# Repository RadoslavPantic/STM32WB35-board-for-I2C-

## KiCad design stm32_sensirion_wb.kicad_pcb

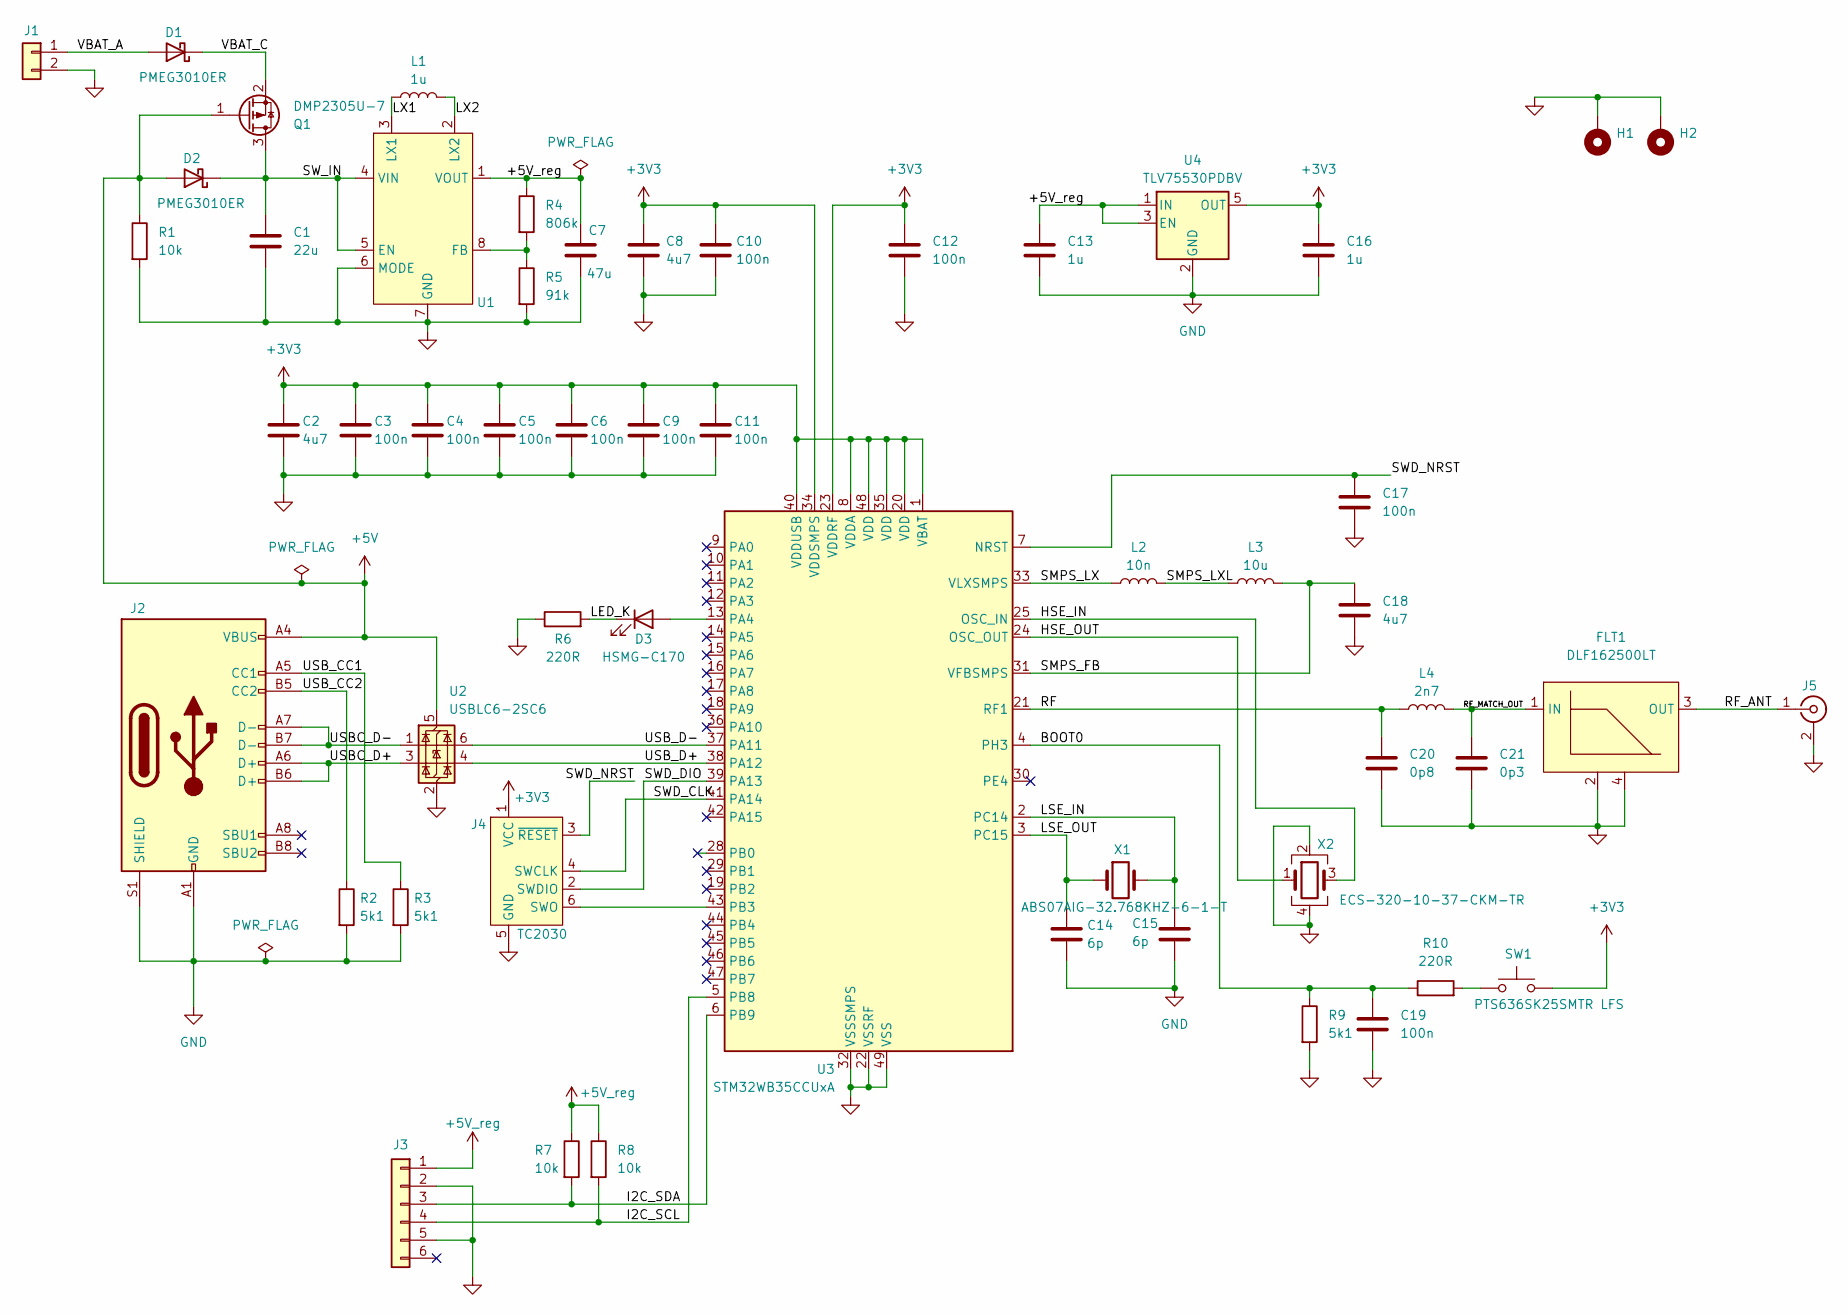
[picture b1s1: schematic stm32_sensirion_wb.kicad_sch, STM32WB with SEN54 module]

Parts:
C1: 22u; C_1206_3216Metric
C2, C8, C18: 4u7; C_0603_1608Metric
C3, C4, C5, C6, C9, C10, C11, C12, C17, C19: 100n; C_0603_1608Metric
C7: 47u; C_1206_3216Metric
C13, C16: 1u; C_0603_1608Metric
C14, C15: 6p; C_0603_1608Metric
C20: 0p8; C_0603_1608Metric
C21: 0p3; C_0603_1608Metric
D1, D2: PMEG3010ER; Nexperia_CFP3_SOD-123W
D3: HSMG-C170; D_0805_2012Metric
FLT1: DLF162500LT; DLF162500LT-5028A1
H1, H2: MountingHole_Pad; MountingHole_2.2mm_M2_Pad_Via
J1: Conn_01x02; PinHeader_1x02_P2.54mm_Vertical
J2: USB_C_Receptacle_USB2.0_16P; USB_C_Receptacle_GCT_USB4105-xx-A_16P_TopMnt_Horizontal
J3: Conn_01x06; PinHeader_1x06_P2.54mm_Vertical
J4: TC2030; Tag-Connect_TC2030-IDC-FP_2x03_P1.27mm_Vertical
J5: Conn_Coaxial; U.FL_Hirose_U.FL-R-SMT-1_Vertical
L1: 1u; L_0805_2012Metric
L2: 10n; L_0603_1608Metric
L3: 10u; L_0805_2012Metric
L4: 2n7; L_0603_1608Metric
Q1: DMP2305U-7; SOT-23
R1, R7, R8: 10k; R_0603_1608Metric
R2, R3, R9: 5k1; R_0603_1608Metric
R4: 806k; R_0603_1608Metric
R5: 91k; R_0603_1608Metric
R6, R10: 220R; R_0603_1608Metric
SW1: PTS636SK25SMTR LFS; SW_SPST_CK_RS282G05A3
U1: TPS631000DRLR; SOT-583-8
U2: USBLC6-2SC6; SOT-23-6
U3: STM32WB35CCUxA; QFN-48-1EP_7x7mm_P0.5mm_EP5.6x5.6mm
U4: TLV75530PDBV; SOT-23-5
X1: ABS07AIG-32.768KHZ-6-1-T; Crystal_SMD_3215-2Pin_3.2x1.5mm
X2: ECS-320-10-37-CKM-TR; Crystal_SMD_SeikoEpson_FA128-4Pin_2.0x1.6mm

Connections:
+3V3: C2.1, C3.1, C4.1, C5.1, C6.1, C8.1, C9.1, C10.1, C11.1, C12.1, C16.1, J4.1 (VCC), SW1.2, U3.1 (VBAT), U3.8 (VDDA), U3.20 (VDD), U3.23 (VDDRF), U3.34 (VDDSMPS), U3.35 (VDD), U3.40 (VDDUSB), U3.48 (VDD), U4.5 (OUT)
+5V: D2.2 (A), J2.A4 (VBUS), J2.A9 (VBUS), J2.B4 (VBUS), J2.B9 (VBUS), Q1.1 (G), R1.1, U2.5 (VBUS)
+5V_reg: C7.1, C13.1, J3.1, R4.1, R7.1, R8.1, U1.1 (VOUT), U4.1 (IN), U4.3 (EN)
/BOOT0: C19.1, R9.1, R10.1, U3.4 (PH3)
/HSE_IN: U3.25 (OSC_IN), X2.3
/HSE_OUT: U3.24 (OSC_OUT), X2.1
/I2C_SCL: J3.4, R8.2, U3.5 (PB8)
/I2C_SDA: J3.3, R7.2, U3.6 (PB9)
/LED_K: D3.1 (K), R6.2
/LSE_IN: C15.1, U3.2 (PC14), X1.2
/LSE_OUT: C14.1, U3.3 (PC15), X1.1
/LX1: L1.1, U1.3 (LX1)
/LX2: L1.2, U1.2 (LX2)
/RF: C20.1, L4.1, U3.21 (RF1)
/RF_ANT: FLT1.3 (OUT), J5.1 (In)
/RF_MATCH_OUT: C21.1, FLT1.1 (IN), L4.2
/SMPS_FB: C18.2, L3.2, U3.31 (VFBSMPS)
/SMPS_LX: L2.1, U3.33 (VLXSMPS)
/SMPS_LXL: L2.2, L3.1
/SWD_CLK: J4.4 (SWCLK), U3.41 (PA14)
/SWD_DIO: J4.2 (SWDIO), U3.39 (PA13)
/SWD_NRST: C17.1, J4.3 (~RESET), U3.7 (NRST)
/SW_IN: C1.1, D2.1 (K), Q1.3 (D), U1.4 (VIN), U1.5 (EN)
/USBC_D+: J2.A6 (D+), J2.B6 (D+), U2.3 (I/O2)
/USBC_D-: J2.A7 (D-), J2.B7 (D-), U2.1 (I/O1)
/USB_CC1: J2.A5 (CC1), R3.1
/USB_CC2: J2.B5 (CC2), R2.1
/USB_D+: U2.4 (I/O2), U3.38 (PA12)
/USB_D-: U2.6 (I/O1), U3.37 (PA11)
/VBAT_A: D1.2 (A), J1.1
/VBAT_C: D1.1 (K), Q1.2 (S)
GND: C1.2, C2.2, C3.2, C4.2, C5.2, C6.2, C7.2, C8.2, C9.2, C10.2, C11.2, C12.2, C13.2, C14.2, C15.2, C16.2, C17.2, C18.1, C19.2, C20.2, C21.2, FLT1.2, FLT1.4, H1.1, H2.1, J1.2, J2.A1 (GND), J2.A12 (GND), J2.B1 (GND), J2.B12 (GND), J2.S1 (SHIELD), J3.2, J3.5, J4.5 (GND), J5.2 (Ext), R1.2, R2.2, R3.2, R5.2, R6.1, R9.2, U1.6 (MODE), U1.7 (GND), U2.2 (GND), U3.22 (VSSRF), U3.32 (VSSSMPS), U3.49 (VSS), U4.2 (GND), X2.2, X2.4
unnamed: D3.2 (A), U3.13 (PA4)
unnamed: J4.6 (SWO), U3.43 (PB3)
unnamed: R10.2, SW1.1
unnamed: R4.2, R5.1, U1.8 (FB)

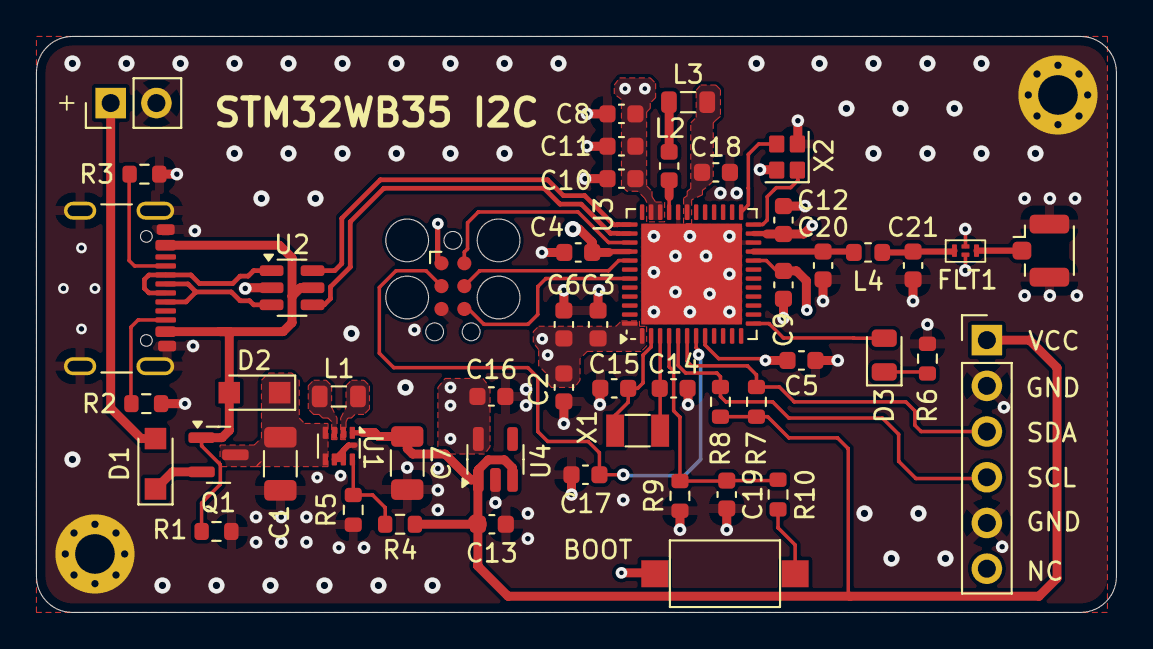
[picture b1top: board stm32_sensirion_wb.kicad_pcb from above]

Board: 4 copper layers, 60.0 x 32.0 mm, 54 parts (0 on the bottom side), 36 nets.

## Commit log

2025-10-29 Initial commit: KiCad STM32WB35 board (SEN66, USB/battery power-path, ESD, BOOT)
2025-10-29 Initial commit: STM32WB35 I2C weather station board (KiCad)
2025-10-29 Remove unnecessary files: filename1.txt, filename2.jpg
